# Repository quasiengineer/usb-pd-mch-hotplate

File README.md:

# USB-powered hot plate

Video about this project:

## Board

Schematics in [pdf format](./pcb/usb-pd-mch-hotplate.pdf)

Archive with gerber files and drill locations could be found [here](./pcb/manufacturing/manufacturing.zip)

Bill of material in [CSV format](./pcb/usb-pd-mch-hotplate.csv)

|Reference              |Value        |Mouser Part Number  |Qty|DNP|
|-----------------------|-------------|--------------------|---|---|
|C1                     |4u7          |187-CL21A475KPFNNNF |1  |   |
|C2                     |1u           |187-CL21B105MBFNNNE |1  |   |
|C3,C4,C5,C6,C10,C11,C13|100n         |187-CL21B104KACNNND |7  |   |
|C7,C8                  |10p          |603-CC805JRNPO9BN100|2  |   |
|C9,C12                 |1u           |187-CL21B105KPFNNNE |2  |   |
|D1                     |Red          |710-150080RS75000   |1  |   |
|D2                     |Green        |710-150080GS75000   |1  |   |
|FB1                    |500mA        |652-MH2029-301Y     |1  |   |
|J1                     |Termosensor  |305-234832          |1  |   |
|J2                     |Type-C       |656-DX07S016JA1R1500|1  |   |
|J4                     |Debug        |649-1012937990604BLF|1  |   |
|J6                     |MCH          |710-66100211722     |1  |   |
|J8                     |Display      |649-10027011-404HLF |1  |   |
|L1                     |27n          |652-CE201210-27NJ   |1  |   |
|Q1                     |IRLR8726     |942-IRLR8726TRPBF   |1  |   |
|R1,R7,R9,R10,R11       |10k          |603-RC0805FR-1010KL |5  |   |
|R2,R5                  |2k2          |603-RC0805FR-072K2L |2  |   |
|R3                     |8k66         |603-AC0805JR-073K3L |1  |   |
|R4                     |4k7          |603-RC0805FR-074K7P |1  |   |
|R6                     |50           |603-AC0805FR-07100RL|1  |   |
|R8                     |220          |603-RT0805FRE07220RL|1  |   |
|S1                     |START_STOP   |612-TL1250F180GQRCLR|1  |   |
|SW1                    |BOOT         |611-TDD01H0SB1R     |1  |   |
|SW2                    |RESET        |611-PTS645VH312     |1  |   |
|SW4                    |UP           |611-PTS645VL582     |1  |   |
|SW5                    |DOWN         |611-PTS645VL582     |1  |   |
|U1                     |STM32G431CBTx| 511-STM32G431CBT6  |1  |   |
|U3                     |TLV701       |595-TLV70133DBVRM3  |1  |   |
|Y1                     |16Mhz, CL=10p|81-XRCGB16M000FXN02R|1  |   |

## Assembly

### Chassis

Step file for [board case](./chassis/PCB chassis.STEP)

Step file for [MCH holder](./chassis/MCH holder.STEP). Please note that it's better to adjust model for exact dimensions of MCH plate (plus some tolerance).

### Hardware and extra parts

- MCH itself, 50x50x2mm, up to 24V, 150W
- steel washers, M2x5, 0.2mm thick, 8 pcs
- ceramic fiber paper
- brass inserts, M2xL4xOD3, 4 pcs
- steel standoffs, M2xL25, 4 pcs
- bolts for MCH holder mount, M2xL6xOD4, 4pcs
- NTC 100k thermistor, 	871-B57703M1104A002
- display, DFRobot DFR0647
- bolts for display mount, 144-04M020040HN, 4pcs
- nuts for display mount, 144-50M020040F004, 4pcs
- thermosensor connector, 305-364198
- thermosensor connector terminals, 305-464766 2pcs
- MCH element connector, 710-661002151922
- display connectors, 649-65039-033ELF, 2pcs
- display connector terminals, 649-47217-000LF, 8pcs
- kapton tape
- high temperature silicone sealant, K2 B205N

### Assembly steps

1. Install heat set inserts into PCB chassis
2. Place PCB inside chassis
3. Put washers from ceramic fiber paper at the mounting holes
4. Put steel washers above ceramic fiber paper washers
5. Screw standoffs to chassis mounting holes
6. Install display to the display slot by using 4 bolts and 4 nuts
7. Connect display to the board by using 4-pin cable
8. Glue thermo sensor to the MCH element
9. Better isolate MCH wires to avoid electrical contact with MCH holder
10. Place MCH plate into MCH holder and route wires from thermo sensor and MCH element itself through corresponding holes
11. Crimp connectors to thermo sensor and MCH element wires
12. Connect thermo sensor and MCH element to the female connectors on the board
13. Put steel washers to the upper part of standoffs 
14. Put washers from ceramic fiber paper above steel washers
15. Place MCH holder to standoffs and screw it

## Firmware

There is compiled [hex file](./firmware/bin/usb-pd-mch-hotplate.hex) in repository, that could be flashed to PCB.

Make sure that `BOOT` switch lever shifted in direction of logo and connect the board via USB and use stm32 programming software. I am using stm32programmer.

## Software

Make sure that `BOOT` switch lever shifted in direction to near board edge and connect the board via USB to USB PD 3.0 compatible power supply that can output at least 100W of power. 

Green LED should be lighting and red LED should be flashing.

Display should show initial menu with the list of programs.

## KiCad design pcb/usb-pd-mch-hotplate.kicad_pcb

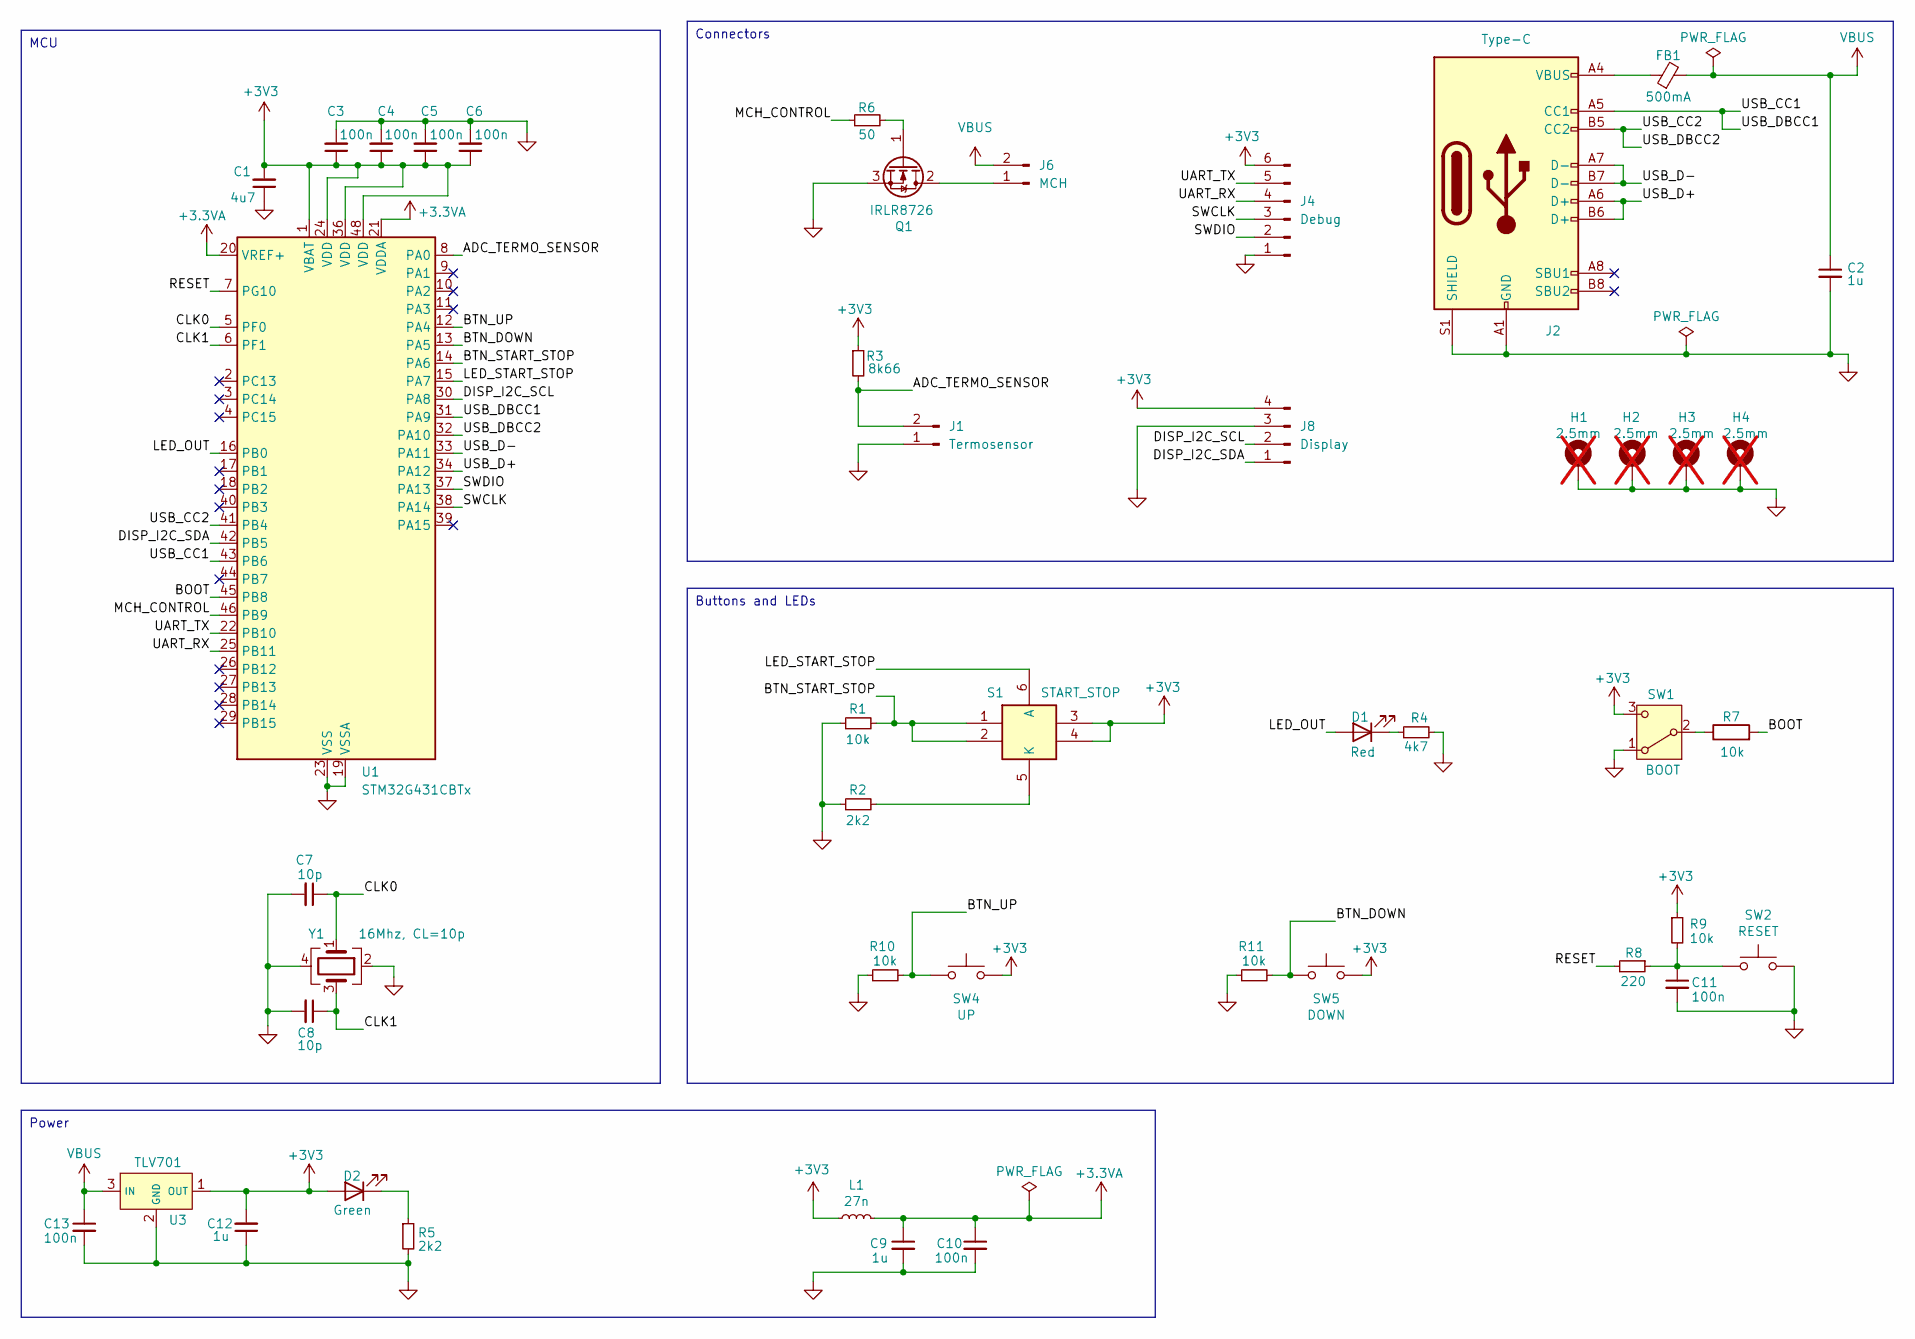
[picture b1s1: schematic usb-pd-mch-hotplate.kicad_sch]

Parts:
C1: 4u7; C_0805_2012Metric_Pad1.18x1.45mm_HandSolder; Mouser Part Number 187-CL21A475KPFNNNF
C2: 1u; C_0805_2012Metric_Pad1.18x1.45mm_HandSolder; Mouser Part Number 187-CL21B105MBFNNNE
C3, C4, C5, C6, C10, C11, C13: 100n; C_0805_2012Metric_Pad1.18x1.45mm_HandSolder; Mouser Part Number 187-CL21B104KACNNND
C7, C8: 10p; C_0805_2012Metric_Pad1.18x1.45mm_HandSolder; Mouser Part Number 603-CC805JRNPO9BN100
C9, C12: 1u; C_0805_2012Metric_Pad1.18x1.45mm_HandSolder; Mouser Part Number 187-CL21B105KPFNNNE
D1: Red; LED_0805_2012Metric_Pad1.15x1.40mm_HandSolder; Mouser Part Number 710-150080RS75000
D2: Green; LED_0805_2012Metric_Pad1.15x1.40mm_HandSolder; Mouser Part Number 710-150080GS75000
FB1: 500mA; L_0805_2012Metric_Pad1.15x1.40mm_HandSolder; Mouser Part Number 652-MH2029-301Y
H1, H2, H3, H4: 2.5mm; MountingHole_2.5mm_Pad_Via; not fitted
J1: Termosensor; 234832E; Mouser Part Number 305-234832
J2: Type-C; USB_C_Receptacle_JAE_DX07S016JA1R1500; Mouser Part Number 656-DX07S016JA1R1500
J4: Debug; PinHeader_1x06_P2.54mm_Horizontal; Mouser Part Number 649-1012937990604BLF
J6: MCH; Conn_66100211722; Mouser Part Number 710-66100211722
J8: Display; PinHeader_1x04_P2.54mm_Horizontal; Mouser Part Number 649-10027011-404HLF
L1: 27n; L_0805_2012Metric_Pad1.15x1.40mm_HandSolder; Mouser Part Number 652-CE201210-27NJ
Q1: IRLR8726; TO-252-2; Mouser Part Number 942-IRLR8726TRPBF
R1, R7, R9, R10, R11: 10k; R_0805_2012Metric_Pad1.20x1.40mm_HandSolder; Mouser Part Number 603-RC0805FR-1010KL
R2, R5: 2k2; R_0805_2012Metric_Pad1.20x1.40mm_HandSolder; Mouser Part Number 603-RC0805FR-072K2L
R3: 8k66; R_0805_2012Metric_Pad1.20x1.40mm_HandSolder; Mouser Part Number 603-AC0805JR-073K3L
R4: 4k7; R_0805_2012Metric_Pad1.20x1.40mm_HandSolder; Mouser Part Number 603-RC0805FR-074K7P
R6: 50; R_0805_2012Metric_Pad1.20x1.40mm_HandSolder; Mouser Part Number 603-AC0805FR-07100RL
R8: 220; R_0805_2012Metric_Pad1.20x1.40mm_HandSolder; Mouser Part Number 603-RT0805FRE07220RL
S1: START_STOP; TL1250F180GQRCLR; Mouser Part Number 612-TL1250F180GQRCLR
SW1: BOOT; SOT175P420X230-3N; Mouser Part Number 611-TDD01H0SB1R
SW2: RESET; PTS645VL582LFS; Mouser Part Number 611-PTS645VH312
SW4: UP; PTS645VL582LFS; Mouser Part Number 611-PTS645VL582
SW5: DOWN; PTS645VL582LFS; Mouser Part Number 611-PTS645VL582
U1: STM32G431CBTx; LQFP-48_7x7mm_P0.5mm; Mouser Part Number 511-STM32G431CBT6
U3: TLV701; SOT-23-5_HandSoldering; Mouser Part Number 595-TLV70133DBVRM3
Y1: 16Mhz, CL=10p; Crystal_SMD_2016-4Pin_2.0x1.6mm; Mouser Part Number 81-XRCGB16M000FXN02R

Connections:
+3.3VA: C9.1, C10.1, L1.2, U1.20 (VREF+), U1.21 (VDDA)
+3V3: C1.2, C3.1, C4.1, C5.1, C6.1, C12.2, D2.2 (A), J4.6, J8.4, L1.1, R3.1, R9.1, SW1.3 (C), U1.1 (VBAT), U1.24 (VDD), U1.36 (VDD), U1.48 (VDD), U3.1 (OUT); also elsewhere on the board
/ADC_TERMO_SENSOR: J1.2, R3.2, U1.8 (PA0)
/BOOT: R7.2, U1.45 (PB8)
/BTN_DOWN: R11.2, U1.13 (PA5); also elsewhere on the board
/BTN_START_STOP: R1.2, S1.1, S1.2, U1.14 (PA6); also elsewhere on the board
/BTN_UP: R10.2, U1.12 (PA4); also elsewhere on the board
/CLK0: C7.1, U1.5 (PF0), Y1.1
/CLK1: C8.1, U1.6 (PF1), Y1.3
/DISP_I2C_SCL: J8.2, U1.30 (PA8)
/DISP_I2C_SDA: J8.1, U1.42 (PB5)
/LED_OUT: D1.2 (A), U1.16 (PB0)
/LED_START_STOP: S1.6 (A), U1.15 (PA7); also elsewhere on the board
/MCH_CONTROL: R6.1, U1.46 (PB9)
/RESET: R8.2, U1.7 (PG10)
/SWCLK: J4.3, U1.38 (PA14)
/SWDIO: J4.2, U1.37 (PA13)
/UART_RX: J4.4, U1.25 (PB11)
/UART_TX: J4.5, U1.22 (PB10)
/USB_CC1: J2.A5 (CC1), U1.31 (PA9), U1.43 (PB6)
/USB_CC2: J2.B5 (CC2), U1.32 (PA10), U1.41 (PB4)
/USB_D+: J2.A6 (D+), J2.B6 (D+), U1.34 (PA12)
/USB_D-: J2.A7 (D-), J2.B7 (D-), U1.33 (PA11)
GND: C1.1, C2.2, C3.2, C4.2, C5.2, C6.2, C7.2, C8.2, C9.2, C10.2, C11.2, C12.1, C13.2, H1.1, H2.1, H3.1, H4.1, J1.1, J2.A1 (GND), J2.A12 (GND), J2.B1 (GND), J2.B12 (GND), J2.S1 (SHIELD), J4.1, J8.3, Q1.3 (S), R1.1, R2.1, R4.2, R5.2, R10.1, R11.1, SW1.1 (A), U1.19 (VSSA), U1.23 (VSS), U1.35 (VSS), U1.47 (VSS), U3.2 (GND), Y1.2, Y1.4; also elsewhere on the board
unnamed 24: C11.1, R8.1, R9.2, SW2.1; also elsewhere on the board
unnamed: D1.1 (K), R4.1
unnamed: D2.1 (K), R5.1
unnamed: FB1.1, J2.A4 (VBUS), J2.A9 (VBUS), J2.B4 (VBUS), J2.B9 (VBUS)
unnamed: J6.1, Q1.2 (D)
unnamed: Q1.1 (G), R6.2
unnamed 30: R2.2, S1.5 (K); also elsewhere on the board
unnamed: R7.1, SW1.2 (B)
VBUS: C2.1, C13.1, FB1.2, J6.2, U3.3 (IN)

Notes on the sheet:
Buttons and LEDs
Power
MCU
Connectors

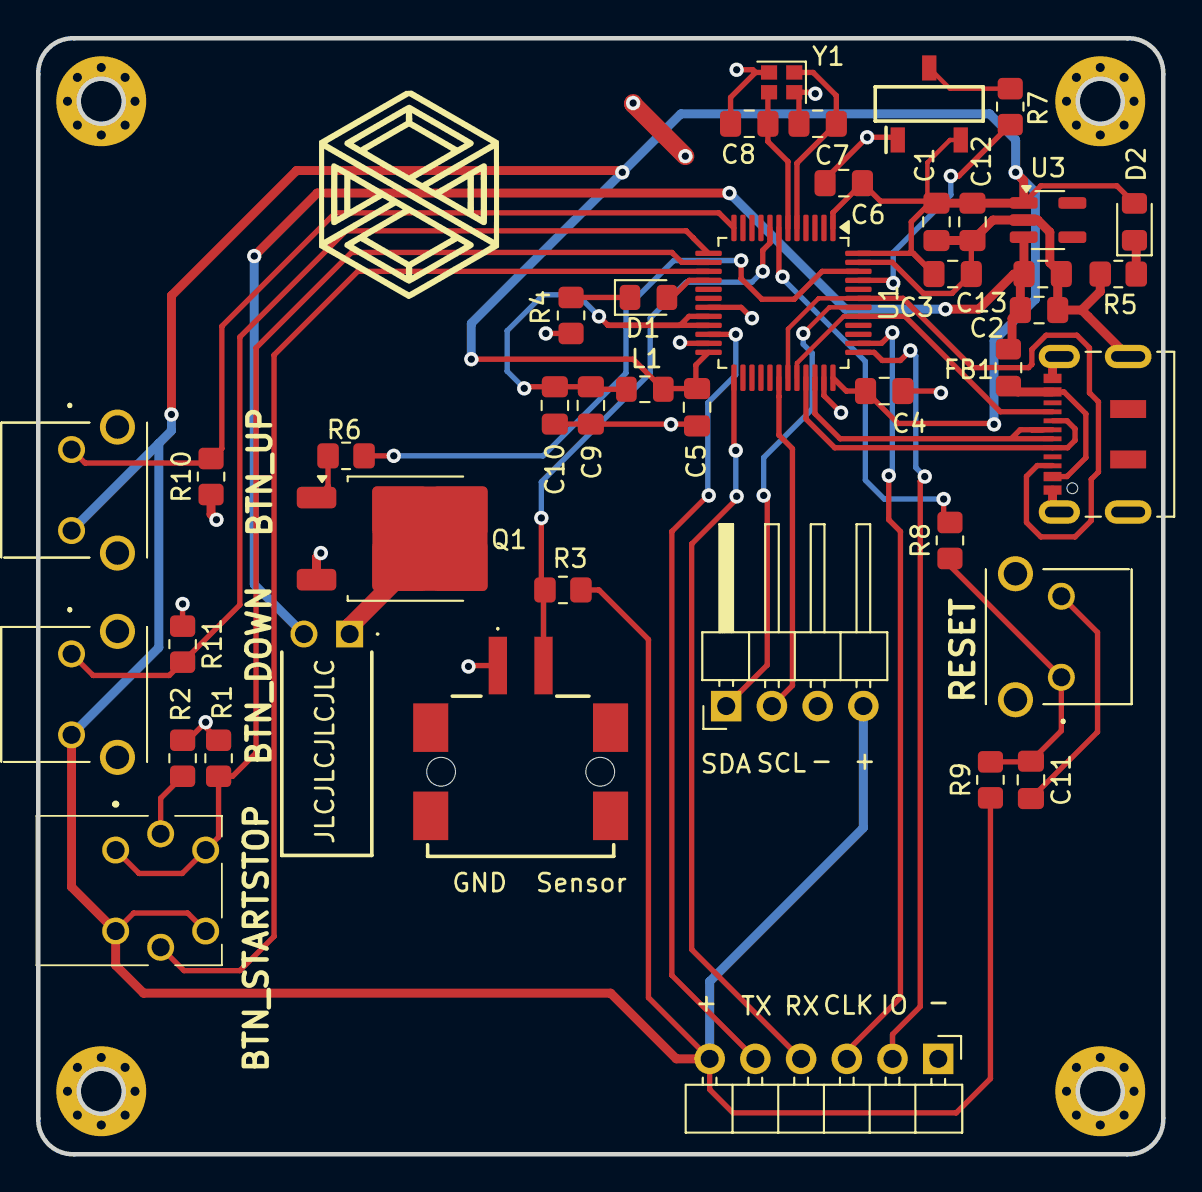
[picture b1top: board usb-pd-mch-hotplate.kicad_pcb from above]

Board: 2 copper layers, 62.5 x 62.0 mm, 46 parts (0 on the bottom side), 33 nets.

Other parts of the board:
BTN_DOWN: DOWN; PTS645VL582LFS
BTN_STARTSTOP: START_STOP; TL1250F180GQRCLR
BTN_UP: UP; PTS645VL582LFS
RESET: RESET; PTS645VL582LFS

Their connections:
+3V3: BTN_DOWN.2, BTN_STARTSTOP.3, BTN_STARTSTOP.4, BTN_UP.2; also elsewhere on the board
/BTN_DOWN: BTN_DOWN.1; also elsewhere on the board
/BTN_START_STOP: BTN_STARTSTOP.1, BTN_STARTSTOP.2; also elsewhere on the board
/BTN_UP: BTN_UP.1; also elsewhere on the board
/LED_START_STOP: BTN_STARTSTOP.6 (A); also elsewhere on the board
GND: RESET.2; also elsewhere on the board
unnamed 24: RESET.1; also elsewhere on the board
unnamed 30: BTN_STARTSTOP.5 (K); also elsewhere on the board

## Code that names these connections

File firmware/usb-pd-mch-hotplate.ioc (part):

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Mcu.Name=STM32G431C(6-8-B)Tx
Mcu.Package=LQFP48
Mcu.UserName=STM32G431CBTx
PA0.GPIOParameters=GPIO_Label
PA0.GPIO_Label=ADC_TERMO_SENSOR
PA0.Mode=IN1-Single-Ended
PA0.Signal=ADC1_IN1
PA10.Mode=EnableDeadBattery
PA10.Signal=UCPD1_DBCC2
PA13.Mode=Trace_Asynchronous_SW
PA13.Signal=SYS_JTMS-SWDIO
PA14.Mode=Trace_Asynchronous_SW
PA14.Signal=SYS_JTCK-SWCLK
PA4.GPIOParameters=GPIO_PuPd,GPIO_Label
PA4.GPIO_Label=BTN_UP
PA4.GPIO_PuPd=GPIO_PULLDOWN
PA4.Signal=GPIO_Input
PA5.GPIOParameters=GPIO_PuPd,GPIO_Label
PA5.GPIO_Label=BTN_DOWN
PA5.GPIO_PuPd=GPIO_PULLDOWN
PA5.Signal=GPIO_Input
PA6.GPIOParameters=GPIO_PuPd,GPIO_Label
PA6.GPIO_Label=BTN_START_STOP
PA6.GPIO_PuPd=GPIO_PULLDOWN
PA6.Signal=GPIO_Input
PA7.GPIOParameters=GPIO_Label
PA7.GPIO_Label=LED_START_STOP
PA7.Signal=GPIO_Output
PA8.GPIOParameters=GPIO_Speed,GPIO_Label,GPIO_Pu
PA8.GPIO_Label=DISP_I2C_SCL
PA8.GPIO_Pu=GPIO_PULLUP
PA8.GPIO_Speed=GPIO_SPEED_FREQ_VERY_HIGH
PA8.Mode=I2C
PA8.Signal=I2C3_SCL
PA9.Mode=EnableDeadBattery
PA9.Signal=UCPD1_DBCC1
PB0.GPIOParameters=GPIO_Label
PB0.GPIO_Label=LED_OUT
PB0.Signal=GPIO_Output
PB10.Mode=Asynchronous
PB10.Signal=USART3_TX
PB11.Mode=Asynchronous
PB11.Signal=USART3_RX
PB3.Mode=Trace_Asynchronous_SW
PB3.Signal=SYS_JTDO-SWO
PB4.Mode=Sink_AllSignals
PB4.Signal=UCPD1_CC2
PB5.GPIOParameters=GPIO_Speed,GPIO_Label,GPIO_Pu
PB5.GPIO_Label=DISP_I2C_SDA
PB5.GPIO_Pu=GPIO_PULLUP
PB5.GPIO_Speed=GPIO_SPEED_FREQ_VERY_HIGH
PB5.Mode=I2C
PB5.Signal=I2C3_SDA
PB6.Mode=Sink_AllSignals
PB6.Signal=UCPD1_CC1
PB9.GPIOParameters=GPIO_Speed,GPIO_Label,GPIO_FM9
PB9.GPIO_FM9=SYSCFG_FASTMODEPLUS_PB9
PB9.GPIO_Label=MCH_CONTROL
PB9.GPIO_Speed=GPIO_SPEED_FREQ_VERY_HIGH
PB9.Signal=S_TIM4_CH4
PF0-OSC_IN.Mode=HSE-External-Oscillator
PF0-OSC_IN.Signal=RCC_OSC_IN
PF1-OSC_OUT.Mode=HSE-External-Oscillator
PF1-OSC_OUT.Signal=RCC_OSC_OUT
RCC.HSE_VALUE=16000000
RCC.SYSCLKFreq_VALUE=168000000
RCC.SYSCLKSource=RCC_SYSCLKSOURCE_PLLCLK
board=custom

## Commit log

2024-07-19 initial
2024-07-19 fix links
2024-07-19 fix links #2
2024-07-19 fix links #3
2024-07-19 list more required items for successful build
2024-07-22 add youtube video thumbnail
